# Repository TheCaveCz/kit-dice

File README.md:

# Throwing Dice / Hrací Kostka

## Česky

Stavebnice elektronické hrací kostky. Zmáčkni tlačítko start a nech pracovat náhodu.

* [Návod na stavbu](doc/manual-cz.md) ([PDF](doc/manual-cz.pdf))
* [Nahrání nového firmware](doc/firmware-cz.md)

## English

Coming coon...

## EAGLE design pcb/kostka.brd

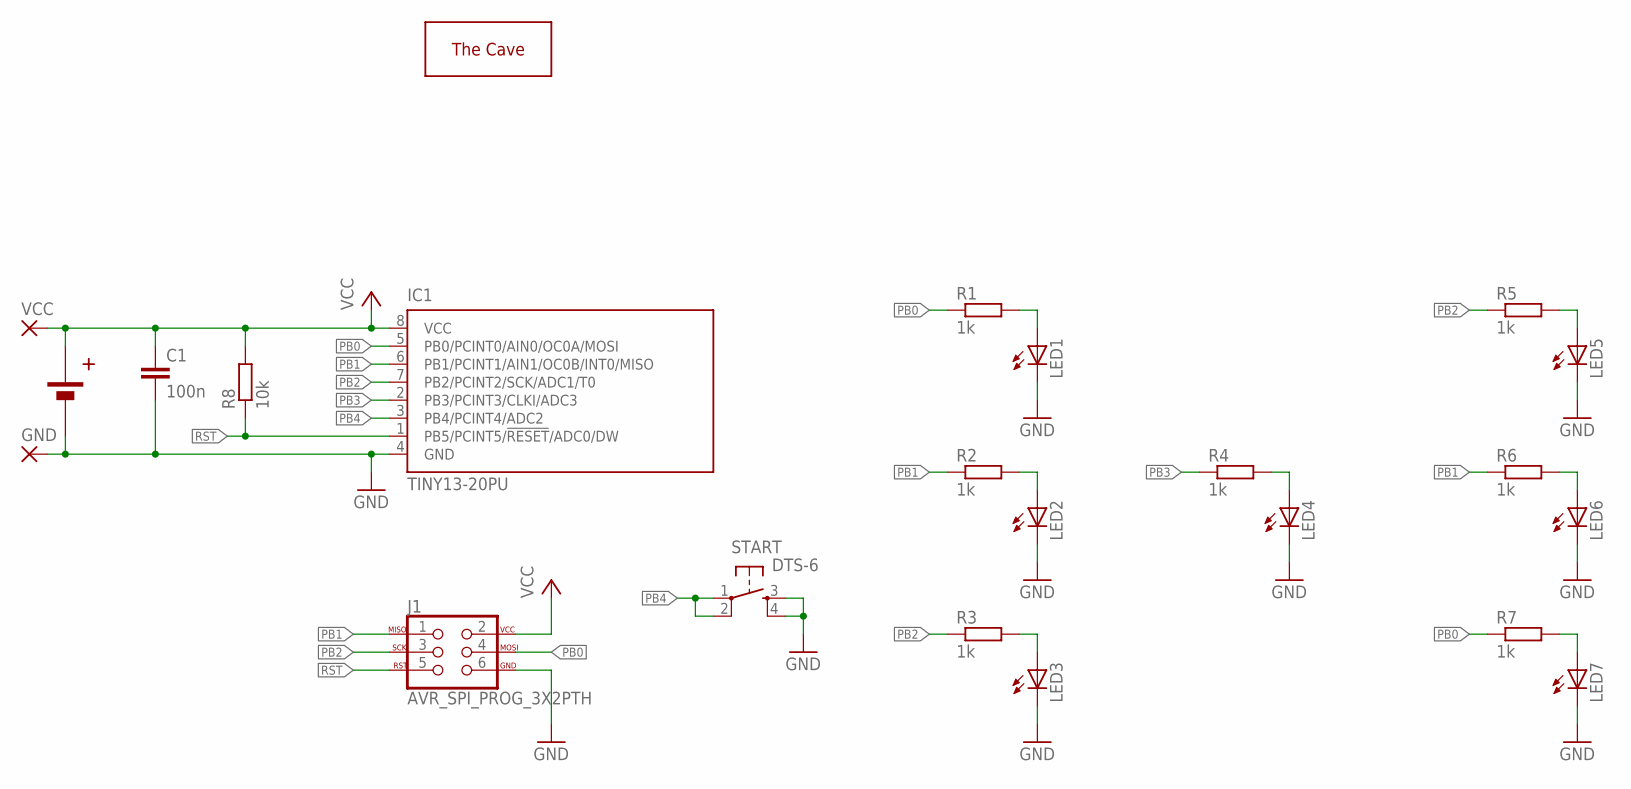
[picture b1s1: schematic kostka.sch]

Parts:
C1: 100n; C025-025X050
GND: WIREPADSMD1,27-254; SMD1,27-2,54
IC1: TINY13-20PU; DIL08
J1: AVR_SPI_PROG_3X2PTH; 2X3
LED1, LED2, LED3, LED4, LED5, LED6, LED7: LED5MM
R1, R2, R3, R4, R5, R6, R7: 1k; 0207/7
R8: 10k; 0207/7
START: DTS-6
U$1: THECAVE_LOGO_NEW_BOTTOM; NEW_LOGO_BOTTOM
VCC: WIREPADSMD1,27-254; SMD1,27-2,54
X1: CR2032H_HOLD2; CR2032HZ

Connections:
GND: C1.2, GND.1, IC1.4 (GND), J1.6, LED1.K (C), LED2.K (C), LED3.K (C), LED4.K (C), LED5.K (C), LED6.K (C), LED7.K (C), START.3, START.4, X1.MINUS (GND)
unnamed: LED5.A, R5.2
unnamed: LED6.A, R6.2
unnamed: LED7.A, R7.2
unnamed: LED4.A, R4.2
unnamed: LED3.A, R3.2
unnamed: LED2.A, R2.2
unnamed: LED1.A, R1.2
PB0: IC1.5 (PB0/PCINT0/AIN0/OC0A/MOSI), J1.4, R1.1, R7.1
PB1: IC1.6 (PB1/PCINT1/AIN1/OC0B/INT0/MISO), J1.1, R2.1, R6.1
PB2: IC1.7 (PB2/PCINT2/SCK/ADC1/T0), J1.3, R3.1, R5.1
PB3: IC1.2 (PB3/PCINT3/CLKI/ADC3), R4.1
PB4: IC1.3 (PB4/PCINT4/ADC2), START.1, START.2
RST: IC1.1 (PB5/PCINT5/!RESET!/ADC0/DW), J1.5, R8.1
VCC: C1.1, IC1.8 (VCC), J1.2, R8.2, VCC.1, X1.PLUS (VCC)

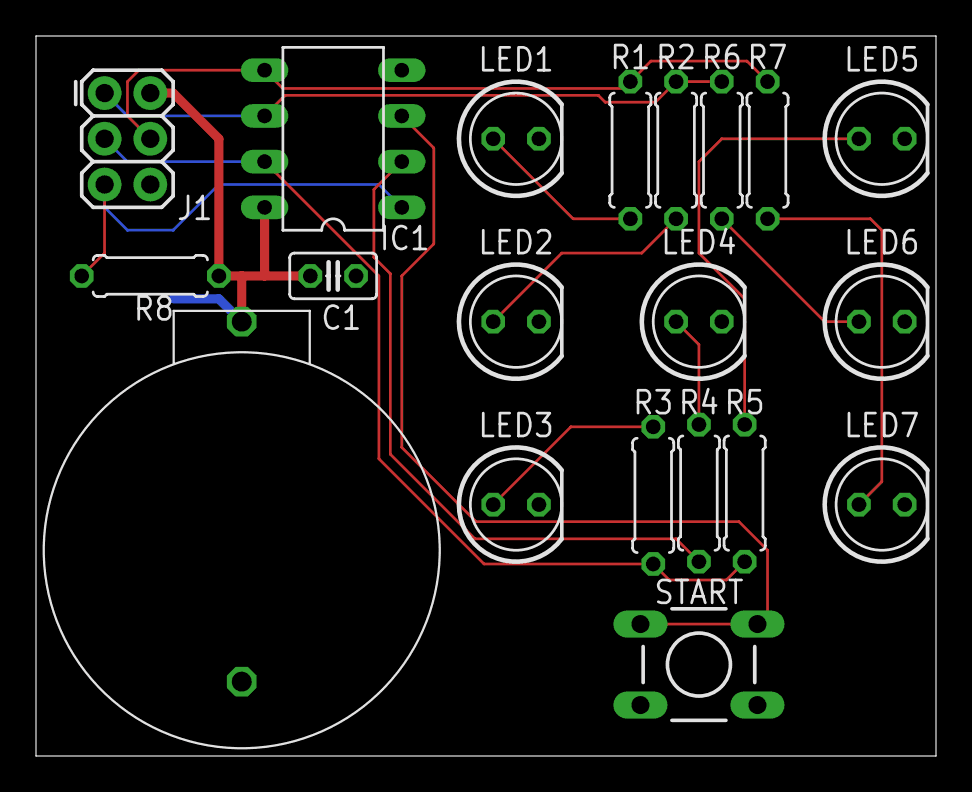
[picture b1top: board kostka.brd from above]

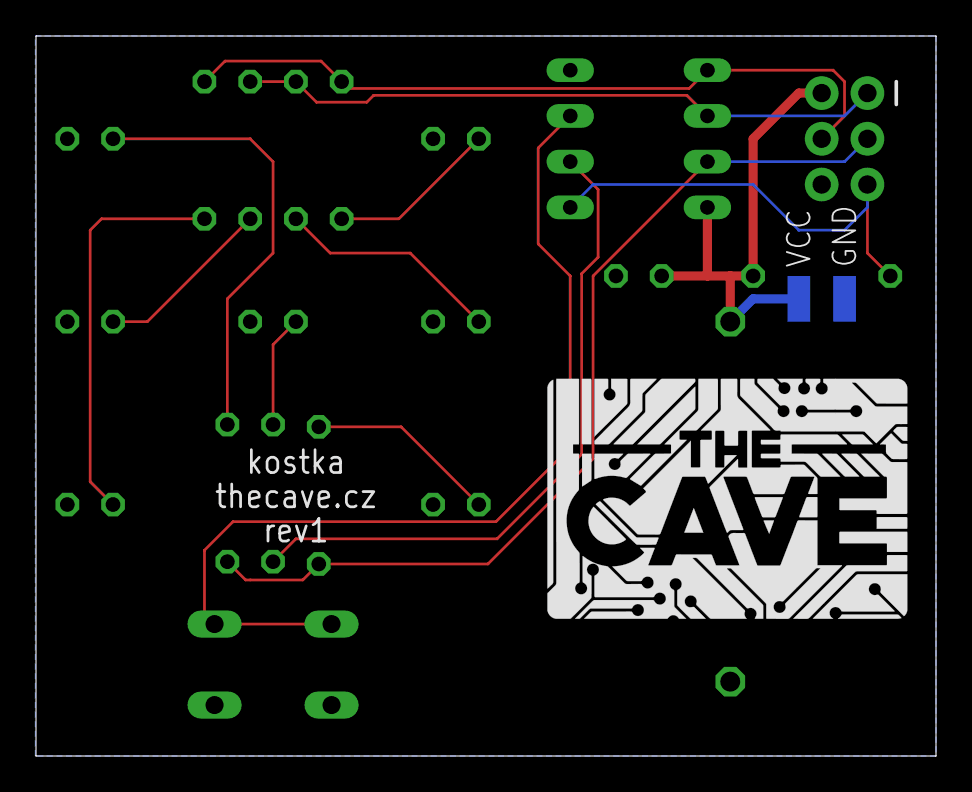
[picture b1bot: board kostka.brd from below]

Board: 2 copper layers, 50.0 x 40.0 mm, 23 parts (2 on the bottom side), 15 nets.

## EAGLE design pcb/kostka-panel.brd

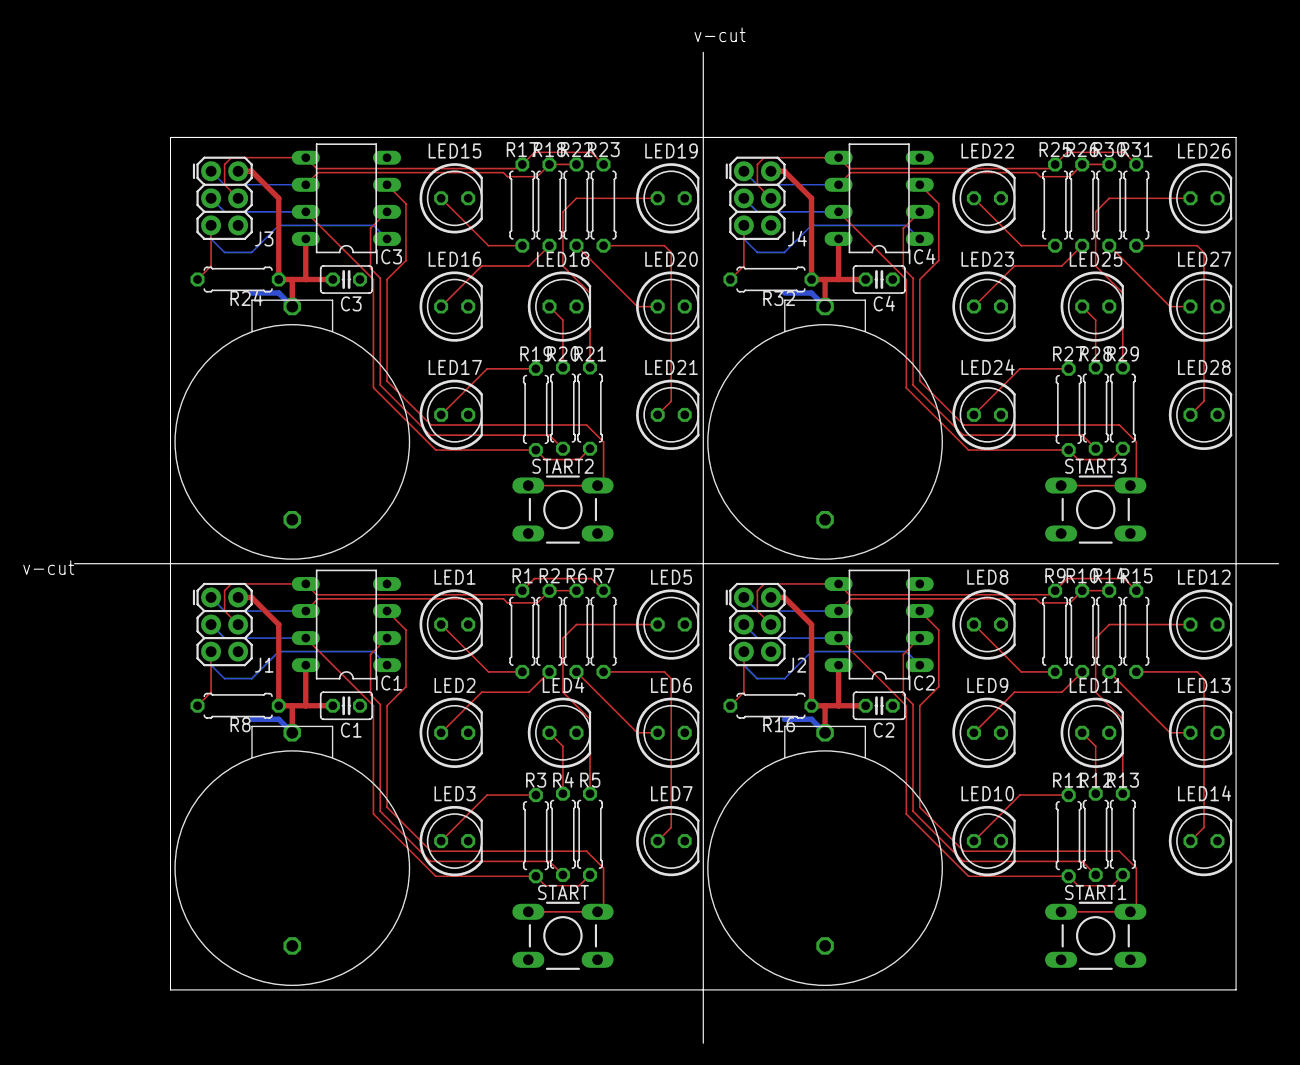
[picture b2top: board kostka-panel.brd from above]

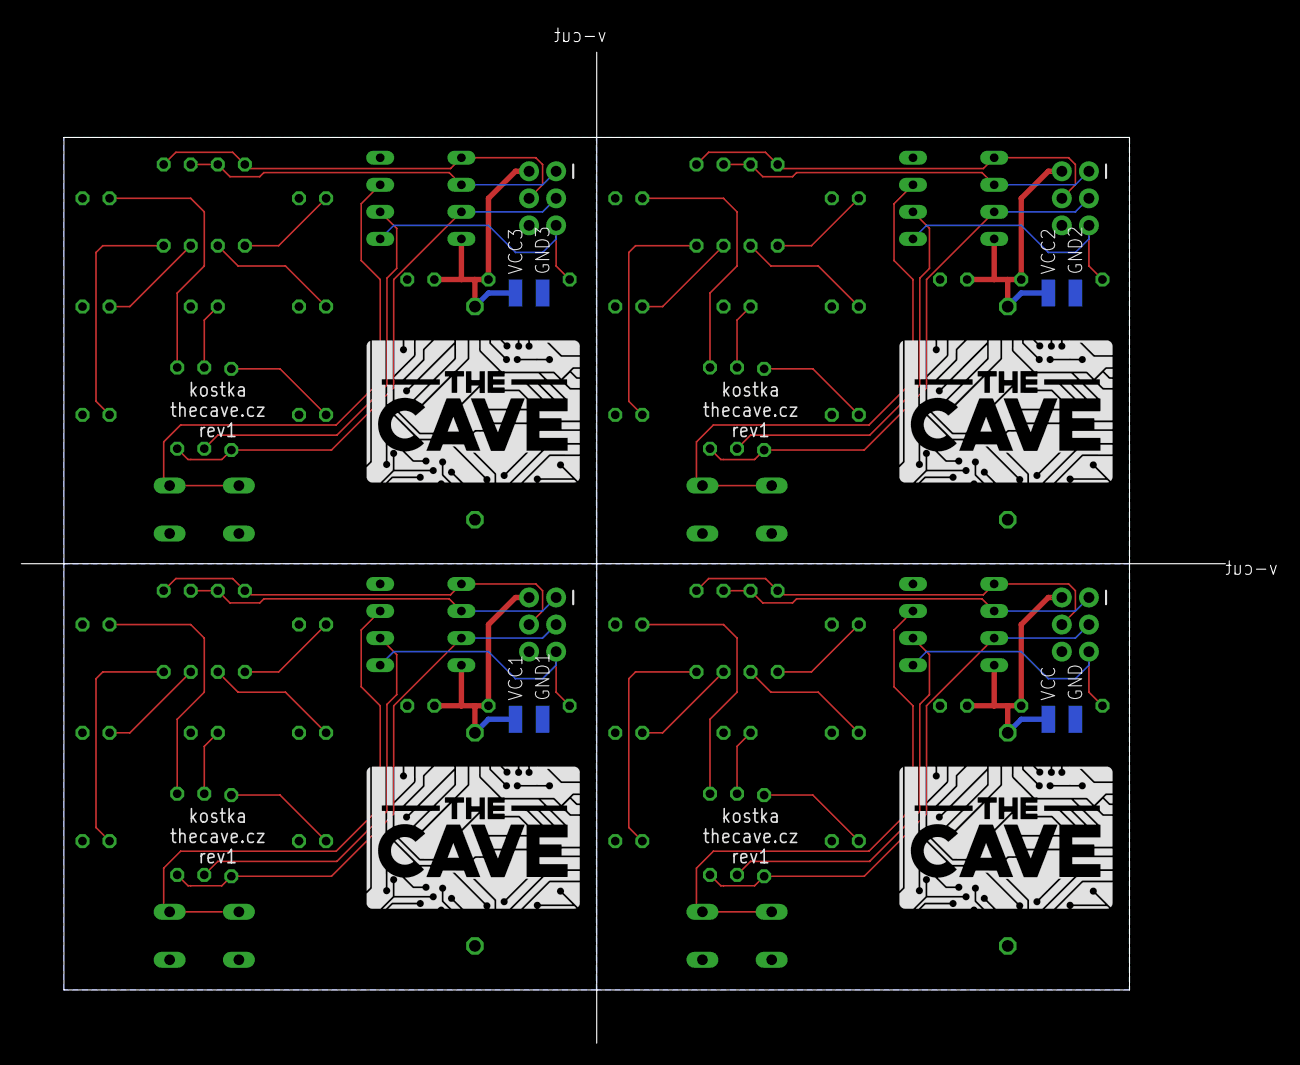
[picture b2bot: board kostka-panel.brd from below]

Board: 2 copper layers, 100.0 x 80.0 mm, 92 parts (8 on the bottom side), 60 nets.

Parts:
C1, C2, C3, C4: 100n; C025-025X050
GND, GND1, GND2, GND3: SMD1,27-2,54
IC1, IC2, IC3, IC4: TINY13-20PU; DIL08
J1, J2, J3, J4: AVR_SPI_PROG_3X2PTH; 2X3
LED1, LED2, LED3, LED4, LED5, LED6, LED7, LED8, LED9, LED10, LED11, LED12, LED13, LED14, LED15, LED16, LED17, LED18, LED19, LED20, LED21, LED22, LED23, LED24, LED25, LED26, LED27, LED28: LED5MM
R1, R2, R3, R4, R5, R6, R7, R9, R10, R11, R12, R13, R14, R15, R17, R18, R19, R20, R21, R22, R23, R25, R26, R27, R28, R29, R30, R31: 1k; 0207/7
R8, R16, R24, R32: 10k; 0207/7
START, START1, START2, START3: DTS-6
U$1, U$2, U$3, U$4: THECAVE_LOGO_NEW_BOTTOM; NEW_LOGO_BOTTOM
VCC, VCC1, VCC2, VCC3: SMD1,27-2,54
X1, X2, X3, X4: CR2032H_HOLD2; CR2032HZ

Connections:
GND: C1.2, GND.1, IC1.4, J1.6, LED1.K, LED2.K, LED3.K, LED4.K, LED5.K, LED6.K, LED7.K, START.3, START.4, X1.MINUS
GND1: C2.2, GND1.1, IC2.4, J2.6, LED8.K, LED9.K, LED10.K, LED11.K, LED12.K, LED13.K, LED14.K, START1.3, START1.4, X2.MINUS
GND2: C3.2, GND2.1, IC3.4, J3.6, LED15.K, LED16.K, LED17.K, LED18.K, LED19.K, LED20.K, LED21.K, START2.3, START2.4, X3.MINUS
GND3: C4.2, GND3.1, IC4.4, J4.6, LED22.K, LED23.K, LED24.K, LED25.K, LED26.K, LED27.K, LED28.K, START3.3, START3.4, X4.MINUS
unnamed: LED12.A, R13.2
unnamed: LED5.A, R5.2
unnamed: LED13.A, R14.2
unnamed: LED6.A, R6.2
unnamed: LED14.A, R15.2
unnamed: LED7.A, R7.2
unnamed: LED11.A, R12.2
unnamed: LED4.A, R4.2
unnamed: LED10.A, R11.2
unnamed: LED3.A, R3.2
unnamed: LED9.A, R10.2
unnamed: LED2.A, R2.2
unnamed: LED8.A, R9.2
unnamed: LED1.A, R1.2
unnamed: LED19.A, R21.2
unnamed: LED20.A, R22.2
unnamed: LED21.A, R23.2
unnamed: LED18.A, R20.2
unnamed: LED17.A, R19.2
unnamed: LED16.A, R18.2
unnamed: LED15.A, R17.2
unnamed: LED26.A, R29.2
unnamed: LED27.A, R30.2
unnamed: LED28.A, R31.2
unnamed: LED25.A, R28.2
unnamed: LED24.A, R27.2
unnamed: LED23.A, R26.2
unnamed: LED22.A, R25.2
PB0: IC1.5, J1.4, R1.1, R7.1
PB1: IC1.6, J1.1, R2.1, R6.1
PB2: IC1.7, J1.3, R3.1, R5.1
PB3: IC1.2, R4.1
PB4: IC1.3, START.1, START.2
PB5: IC2.5, J2.4, R9.1, R15.1
PB6: IC2.6, J2.1, R10.1, R14.1
PB7: IC2.7, J2.3, R11.1, R13.1
PB8: IC2.2, R12.1
PB9: IC2.3, START1.1, START1.2
PB10: IC3.5, J3.4, R17.1, R23.1
PB11: IC3.6, J3.1, R18.1, R22.1
PB12: IC3.7, J3.3, R19.1, R21.1
PB13: IC3.2, R20.1
PB14: IC3.3, START2.1, START2.2
PB15: IC4.5, J4.4, R25.1, R31.1
PB16: IC4.6, J4.1, R26.1, R30.1
PB17: IC4.7, J4.3, R27.1, R29.1
PB18: IC4.2, R28.1
PB19: IC4.3, START3.1, START3.2
RST: IC1.1, J1.5, R8.1
RST1: IC2.1, J2.5, R16.1
RST2: IC3.1, J3.5, R24.1
RST3: IC4.1, J4.5, R32.1
VCC: C1.1, IC1.8, J1.2, R8.2, VCC.1, X1.PLUS
VCC1: C2.1, IC2.8, J2.2, R16.2, VCC1.1, X2.PLUS
VCC2: C3.1, IC3.8, J3.2, R24.2, VCC2.1, X3.PLUS
VCC3: C4.1, IC4.8, J4.2, R32.2, VCC3.1, X4.PLUS

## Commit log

2019-05-09 Add firmware and pcb
2019-05-09 Add pictures
2019-05-14 Add gerber files
2019-06-20 Add manual
2019-06-20 Fix readme links
2019-06-20 Add firmware upload instructions

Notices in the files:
parts and their libraries:
SparkFun-Connectors: Licensing: Creative Commons ShareAlike 4.0 International - https://creativecommons.org/licenses/by-sa/4.0
